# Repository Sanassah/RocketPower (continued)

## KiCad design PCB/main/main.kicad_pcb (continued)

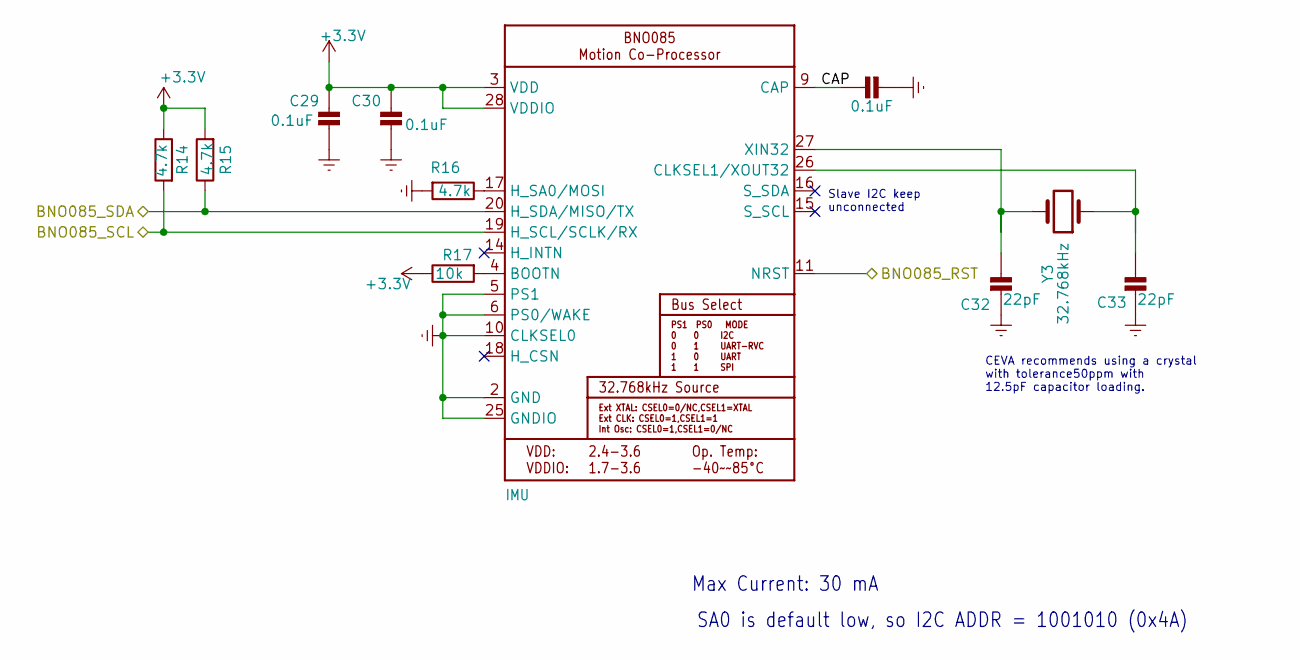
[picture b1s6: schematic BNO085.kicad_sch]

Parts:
BNO1: IMU; BNO085; Mouser Part Number 526-BNO085; LCSC C5189642
C29, C30, C31: 0.1uF; R_0603_1608Metric_Pad0.98x0.95mm_HandSolder; LCSC C1590
C32, C33: 22pF; R_0603_1608Metric_Pad0.98x0.95mm_HandSolder; LCSC C49326308
R14, R15, R16: 4.7k; R_0603_1608Metric_Pad0.98x0.95mm_HandSolder; LCSC C23162
R17: 10k; R_0603_1608Metric_Pad0.98x0.95mm_HandSolder; LCSC C25804
Y3: 32.768kHz; Crystal_SMD_2012-2Pin_2.0x1.2mm_HandSoldering; Mouser Part Number 815-ABS06-32.7K-1-T; LCSC C1985397

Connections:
+3.3V: BNO1.3 (VDD), BNO1.28 (VDDIO), C29.1, C30.1, R14.1, R15.2, R17.1; also elsewhere on the board
/BNO085_RST: BNO1.11 (NRST); also elsewhere on the board
/BNO085_SCL: BNO1.19 (H_SCL/SCLK/RX), R14.2; also elsewhere on the board
/BNO085_SDA: BNO1.20 (H_SDA/MISO/TX), R15.1; also elsewhere on the board
/IMU BNO085/CAP: BNO1.9 (CAP), C31.2
GNDREF: BNO1.2 (GND), BNO1.5 (PS1), BNO1.6 (PS0/WAKE), BNO1.10 (CLKSEL0), BNO1.25 (GNDIO), C29.2, C30.2, C31.1, C32.2, C33.2, R16.2; also elsewhere on the board
unnamed: BNO1.4 (BOOTN), R17.2
unnamed: BNO1.26 (CLKSEL1/XOUT32), C33.1, Y3.1
unnamed: BNO1.17 (H_SA0/MOSI), R16.1
unnamed: BNO1.27 (XIN32), C32.1, Y3.2

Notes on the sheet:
Max Current: 30 mA
SA0 is default low, so I2C ADDR = 1001010 (0x4A)
CEVA recommends using a crystal with tolerance50ppm with 12.5pF capacitor loading.
Slave I2C keep unconnected

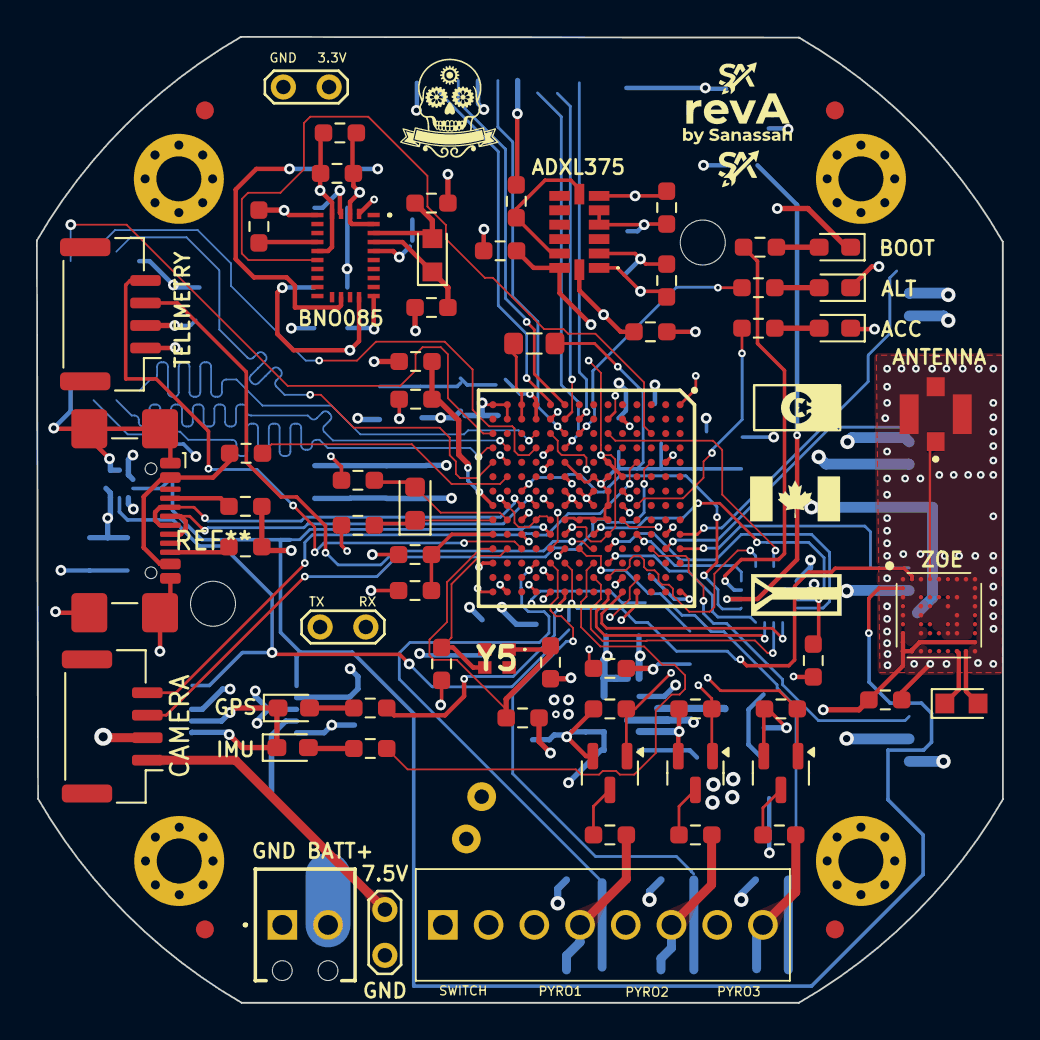
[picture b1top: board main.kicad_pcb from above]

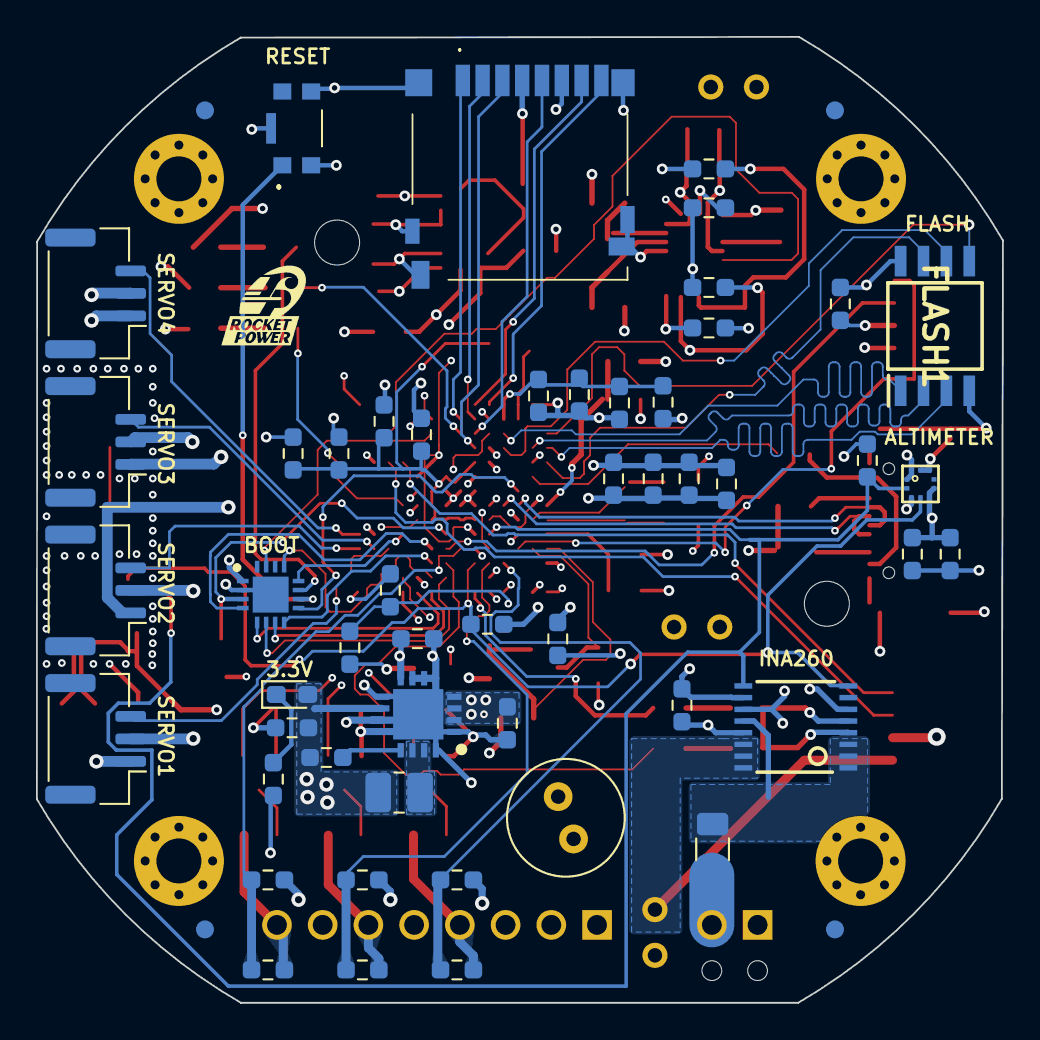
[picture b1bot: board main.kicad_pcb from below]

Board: 4 copper layers, 53.7 x 53.7 mm, 121 parts (55 on the bottom side), 97 nets.

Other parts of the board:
ADXL1: ACC; ADXL375BCCZRL
BMP1: ALTIMETER; BMP388
C34, C35, C37, C40: 0.1uF; R_0603_1608Metric_Pad0.98x0.95mm_HandSolder
C36: 1uF; R_0603_1608Metric_Pad0.98x0.95mm_HandSolder
INA1: INA260; TSSOP16
JST-GH-2: CAMERA; JST_GH_BM04B-GHS-TBT_1x04-1MP_P1.25mm_Vertical
R18, R32: 4.7k; R_0603_1608Metric_Pad0.98x0.95mm_HandSolder
R19: 10k; R_0603_1608Metric_Pad0.98x0.95mm_HandSolder
TP1, TP2, TP3: TestPoint_2Pole; TestPoint_2Pads_Pitch2.54mm_Drill0.8mm

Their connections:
+3.3V: ADXL1.1 (VDD(I/O)), ADXL1.6 (VIN), BMP1.1 (VDDIO), BMP1.5 (SDO), BMP1.6 (CSB), BMP1.10 (VDD), C34.1, C35.1, C36.1, C37.1, C40.1, INA1.10 (VS), R18.1, R19.1, R32.1, TP1.1; also elsewhere on the board
+7.5V: INA1.14 (IN-), INA1.15 (IN-), INA1.16 (IN-), JST-GH-2.1, TP3.1; also elsewhere on the board
+BATT: INA1.1 (IN+), INA1.2 (IN+), INA1.3 (IN+), INA1.12 (VBUS); also elsewhere on the board
/ADXL375_SCL2: ADXL1.14 (SCL), R32.2; also elsewhere on the board
/ADXL375_SDA2: ADXL1.13 (SDA), R18.2; also elsewhere on the board
/BMP390_SCL1: BMP1.2 (SCK), INA1.9 (SCL); also elsewhere on the board
/BMP390_SDA1: BMP1.4 (SDI), INA1.8 (SDA); also elsewhere on the board
/Cam_RX: JST-GH-2.3; also elsewhere on the board
/Cam_TX: JST-GH-2.4; also elsewhere on the board
/Reserve_RX: TP2.2; also elsewhere on the board
/Reserve_TX: TP2.1; also elsewhere on the board
GNDREF: ADXL1.2 (GND@1), ADXL1.4 (GND@2), ADXL1.5 (GND@3), BMP1.3 (GND), BMP1.8 (GND), BMP1.9 (GND), C34.2, C35.2, C36.2, C37.2, C40.2, INA1.4 (A1), INA1.5 (A0), INA1.6 (GND), INA1.11 (GND), INA1.13 (GND), JST-GH-2.2, TP1.2, TP3.2; also elsewhere on the board
unnamed: ADXL1.7 (CS), ADXL1.12 (ADDR/SDO), R19.2

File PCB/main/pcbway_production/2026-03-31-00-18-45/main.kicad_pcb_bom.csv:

Designator,Quantity,Value,Footprint,Package,MPN,DNP,Mount_Type,LCSC,Mouser Part Number,Rating,Description,Type,Height,Mouser Price/Stock,Manufacturer_Name,Arrow Part Number,Arrow Price/Stock,MANUFACTURER
ADXL1,1,ACC,ADXL375BCCZRL,,,,smt,C579466 ,584-ADXL375BCCZ,,,,,,,,,
BMP1,1,ALTIMETER,BMP388,,,,tht,C2684802 ,262-BMP390,,,,,,,,,
BNO1,1,IMU,BNO085,,,,smt,C5189642,526-BNO085,,,,,,,,,
"C1, C11, C28",3,10uF,R_0603_1608Metric_Pad0.98x0.95mm_HandSolder,,,,smt,C70225 ,,25V,,,,,,,,
"C10, C9",2,18pF,R_0603_1608Metric_Pad0.98x0.95mm_HandSolder,,,,smt,C1647 ,,,,,,,,,,
"C12, C13, C17, C18, C19, C20, C21, C22, C26, C5",10,0.22uF,R_0603_1608Metric_Pad0.98x0.95mm_HandSolder,,,,smt,C106216,,,,,,,,,,
"C14, C15, C16, C27, C38, C8",6,4.7uF,R_0603_1608Metric_Pad0.98x0.95mm_HandSolder,,,,smt,C19666 ,,,X5R 4U7 10% 6.3 V,,,,,,,
C2,1,22uF,R_0603_1608Metric_Pad0.98x0.95mm_HandSolder,,,,smt,C2762594,,6.3V,,,,,,,,
"C23, C24",2,10pF,R_0603_1608Metric_Pad0.98x0.95mm_HandSolder,,,,smt,C2168929,,,,,,,,,,
"C25, C7",2,10nF,R_0603_1608Metric_Pad0.98x0.95mm_HandSolder,,,,smt,C149619 ,,,,,,,,,,
"C29, C30, C31, C34, C35, C37, C39",7,0.1uF,R_0603_1608Metric_Pad0.98x0.95mm_HandSolder,,,,smt,C48579250,,,,Ceramic,,,,,,
"C3, C36, C40",3,1uF,R_0603_1608Metric_Pad0.98x0.95mm_HandSolder,,,,smt,C1592 ,,,,Tantalum,,,,,,
"C32, C33",2,22pF,R_0603_1608Metric_Pad0.98x0.95mm_HandSolder,,,,smt,C49326308 ,,,,,,,,,,
C41,1,470uf,C_Radial_D6.3mm_H11.0mm_P2.50mm,,,,tht,C1020067,,,"Polarized capacitor, 16v",,,,,,,
C6,1,2.2uF,R_0603_1608Metric_Pad0.98x0.95mm_HandSolder,,,,smt,C23630 ,,,,,,,,,,
CONMHF1-SMD-G-T1,1,ANTENNA,CONMHF1SMDGT,,CONMHF1-SMD-G-T,,smt,C22442695 ,712-CONMHF1-SMD-G-T,,CONMHF1-SMD-G-T,,1.31,https://www.mouser.co.uk/ProductDetail/TE-Connectivity-Linx-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,TE Connectivity,,,
D1,1,3.3V LED,LED_0603_1608Metric_Pad1.05x0.95mm_HandSolder,,,,smt,C20433785 ,78-TLMG1100-GS15,,,,,,,,,
D2,1,BOOT LED,LED_0603_1608Metric_Pad1.05x0.95mm_HandSolder,,,,smt,C20433785 ,78-TLMG1100-GS15,,,,,,,,,
D3,1,GPS LED,LED_0603_1608Metric_Pad1.05x0.95mm_HandSolder,,,,smt,C20433785 ,78-TLMG1100-GS15,,,,,,,,,
D4,1,Altimeter LED,LED_0603_1608Metric_Pad1.05x0.95mm_HandSolder,,,,smt,C20433785 ,78-TLMG1100-GS15,,,,,,,,,
D5,1,200G ACC LED,LED_0603_1608Metric_Pad1.05x0.95mm_HandSolder,,,,smt,C20433785 ,78-TLMG1100-GS15,,,,,,,,,
D6,1,IMU LED,LED_0603_1608Metric_Pad1.05x0.95mm_HandSolder,,,,smt,C20433785 ,78-TLMG1100-GS15,,,,,,,,,
D7,1,ESD9R3.3ST5G,ESD9R3_3ST5G,,ESD9R3.3ST5G,,smt,C233388 ,863-ESD9R3.3ST5G,,Low Body Height: 0.016 (0.4 mm); Small Body Outline Dimensions: 0.039 x 0.024 (1.00 mm x 0.60 mm); UltraLow Leakage < 1 nA; UltraLow Capacitance 0.5 pF; Low Clamping Voltage; Standoff Voltage: 3.3 V; Response Time < 1.0 ns; IEC6100042 Level 4 ESD Protection; This is a PbFree and HalogenFree Device,,0.4,https://www.mouser.co.uk/ProductDetail/onsemi/ESD9R3.3ST5G?q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,onsemi,,,
DM3D-SF1,1,MicroSD,DM3DSF,,DM3D-SF,,smt,C719027 ,798-DM3D-SF,,Micro SD card push pull manual,,1.55,https://www.mouser.co.uk/ProductDetail/Hirose-Connector/DM3D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,Hirose,,,
F1,1,6A,Fuse_1206_3216Metric,,,,smt,C183157 ,530-C1F6,,,PPTC,,,,,,
"FB1, FB2",2,120,R_0603_1608Metric_Pad0.98x0.95mm_HandSolder,,,,smt,C14709,81-BLM18PG121SN1D,,Ferrite bead,,,,,,,
INA1,1,INA260,TSSOP16,,,,tht,C2155885 ,595-INA260AIPWR,,,,,,,,,
KMR241GLFS1,1,RESET,KMR421GULCLFS,,KMR241GLFS,,smt,C221682 ,611-KMR241GLFS,,KMR241GLFS,,2.5,https://www.mouser.co.uk/ProductDetail/CK/KMR241GLFS?qs=sb%2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,C & K COMPONENTS,,,
L1,1,6.8uH,L_1008_2520Metric_Pad1.43x2.20mm_HandSolder,,,,smt,C307868 ,810-VLS25212HBX6R8M1,,,,,,,,,
L2,1,4.7uH,L_0805_2012Metric_Pad1.05x1.20mm_HandSolder,,,,smt,C397305 ,81-LQM21PN4R7NGRDRD,,,,,,,,,
L3,1,2.2μH,L_0805_2012Metric_Pad1.05x1.20mm_HandSolder,,,,smt,C83998,81-LQM2MPN2R2NG0L,,LQM2MPN2R2NG0L,,,,,,,
MIMXRT1062DVL6B1,1,MCU,BGA196C80P14X14_1200X1200X152,,MIMXRT1062DVL6B,,smt,C2847497,771-MIMXRT1062DVL6B,,MIMXRT1062DVL6B,,1.52,https://www.mouser.co.uk/ProductDetail/NXP-Semiconductors/MI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,NXP,MIMXRT1062DVL6B,https://www.arrow.com/en/products/mimxrt1062dvl6b/nxp-semico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,
MKL02Z32VFG1,1,BOOT,QFN50P300X300X65-17N-D,,MKL02Z32VFG4,Yes,smt,,,,MKL02Z32VFG4,,0.65,https://www.mouser.co.uk/ProductDetail/NXP-Semiconductors/MK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,NXP,MKL02Z32VFG4,https://www.arrow.com/en/products/mkl02z32vfg4/nxp-semicondu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,
"Q1, Q2, Q3",3,SI2302,SOT-23,,,,smt,C460978,621-DMG3406L-7,,,,,,,,,
"R1, R2",2,5.1k,R_0603_1608Metric_Pad0.98x0.95mm_HandSolder,,,,smt,C1647,,,,,,,,,,
R10,1,2.2M,R_0603_1608Metric_Pad0.98x0.95mm_HandSolder,,,,smt,C18679 ,,,,,,,,,,
"R11, R12, R5, R7, R9",5,470,R_0603_1608Metric_Pad0.98x0.95mm_HandSolder,,,,smt,C23179,,,,,,,,,,
R13,1,100k,R_0603_1608Metric_Pad0.98x0.95mm_HandSolder,,,,smt,C14675,,,,,,,,,,
"R14, R15, R16, R6, R8",5,4.7k,R_0603_1608Metric_Pad0.98x0.95mm_HandSolder,,,,smt,C23162 ,,,,,,,,,,
"R17, R18, R19, R20, R23, R24, R27, R28, R31",9,10k,R_0603_1608Metric_Pad0.98x0.95mm_HandSolder,,,,smt,C25804 ,,,,,,,,,,
"R21, R25, R29",3,7,R_0603_1608Metric_Pad0.98x0.95mm_HandSolder,,,,smt,C228062 ,,,,,,,,,,
"R22, R26, R30",3,7k,R_0603_1608Metric_Pad0.98x0.95mm_HandSolder,,,,smt,C23101 ,,,,,,,,,,
R3,1,1M,R_0603_1608Metric_Pad0.98x0.95mm_HandSolder,,,,smt,C22935,,,,,,,,,,
R4,1,1k,R_0603_1608Metric_Pad0.98x0.95mm_HandSolder,,,,smt,C21190 ,,,,,,,,,,
S4B-PH-K-S_LF__SN_1,1,TELEMETRY,JST_GH_BM04B-GHS-TBT_1x04-1MP_P1.25mm_Vertical,,S4B-PH-K-S(LF)(SN),,smt,C161692,306-BM04BGHSTBTLFSNN,,CONN HEADER R/A 4POS 2MM,,4.8,https://www.mouser.co.uk/ProductDetail/JST-Commercial/S4B-PH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,JST (JAPAN SOLDERLESS TERMINALS),,,
S4B-PH-K-S_LF__SN_2,1,CAMERA,JST_GH_BM04B-GHS-TBT_1x04-1MP_P1.25mm_Vertical,,S4B-PH-K-S(LF)(SN),,smt,C161692,306-BM04BGHSTBTLFSNN,,CONN HEADER R/A 4POS 2MM,,4.8,https://www.mouser.co.uk/ProductDetail/JST-Commercial/S4B-PH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,JST (JAPAN SOLDERLESS TERMINALS),,,
SERVO1,1,SERVO1,JST_GH_BM03B-GHS-TBT_1x03-1MP_P1.25mm_Vertical,,,,smt,C161691,306-BM03BGHSTBTLFSNN,,,,,,,,,
SERVO2,1,SERVO2,JST_GH_BM03B-GHS-TBT_1x03-1MP_P1.25mm_Vertical,,,,smt,C161691,306-BM03BGHSTBTLFSNN,,,,,,,,,
SERVO3,1,SERVO3,JST_GH_BM03B-GHS-TBT_1x03-1MP_P1.25mm_Vertical,,,,smt,C161691,306-BM03BGHSTBTLFSNN,,,,,,,,,JST
SERVO4,1,SERVO4,JST_GH_BM03B-GHS-TBT_1x03-1MP_P1.25mm_Vertical,,,,smt,C161691,306-BM03BGHSTBTLFSNN,,,,,,,,,
ScrewTerminal1,1,1725711,1725711,,1725711,,tht,C5476987,651-1725711,,"PCB terminal block - MPT 0,5/ 8-2,54 - 1725711",,8.65,https://www.mouser.co.uk/ProductDetail/Phoenix-Contact/17257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,Phoenix Contact,,,
ScrewTerminal2,1,BATT,1725656,,,,tht,C3029316 ,651-1725656,,"Generic screw terminal, single row, 01x02, script generated (kicad-library-utils/schlib/autogen/connector/)",,,,,,,
TP1,1,TestPoint_2Pole,TestPoint_2Pads_Pitch2.54mm_Drill0.8mm,,,Yes,tht,,,,2-polar test point,,,,,,,
TP2,1,TestPoint_2Pole,TestPoint_2Pads_Pitch2.54mm_Drill0.8mm,,,Yes,tht,,,,2-polar test point,,,,,,,
TP3,1,TestPoint_2Pole,TestPoint_2Pads_Pitch2.54mm_Drill0.8mm,,,Yes,tht,,,,2-polar test point,,,,,,,
TPS62111RSAR1,1,3.3Vreg,TPS62111RSAR,,TPS62111RSAR,,smt,C133558 ,595-TPS62111RSAR,,,,1,https://www.mouser.co.uk/ProductDetail/Texas-Instruments/TPS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,Texas Instruments,,,
U-BLOX_ZOE_M8Q-0-1,1,GPS,UBLOX_ZOE_M8-0-10,,,,tht,C7398634,377-ZOE-M8Q-0,,U-BLOX_ZOE_M8Q-0-10,,,,,,,
USB_C_Receptacle_USB2.0_14P1,1,USBc,USB_C_Receptacle_GCT_USB4110,,,,smt,C5143397,640-USB4110-GF-A,,USB_C_Receptacle_USB2.0_14P,,,,,,,
W25Q64JVXGIM_TR1,1,FLASH,SON80P400X400X50-9N,,W25Q64JVXGIM TR,,smt,C7398634 ,454-W25Q64JVXGIMTR,,W25Q64JVXGIM_TR,,0.5,https://www.mouser.co.uk/ProductDetail/Winbond/W25Q64JVXGIM-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,Winbond,,,
"Y1, Y3",2,32.768kHz,Crystal_SMD_2012-2Pin_2.0x1.2mm_HandSoldering,,,,smt,[Y1]C510776; [Y3]C1985397,[Y1]815-ABS06-32.7K-9-T; [Y3]815-ABS06-32.7K-1-T,,50ppm  -  12.5pF capacitor loading,,,,,,,
Y4,1,32.768kHz,830050789,,,,smt,C7462219,428-202816-MC01,,7 pF  +/- 100 ppm   70 kOhms,,,,,,,
Y5,1,XRCGB24M000F2P29R0,XRCGB,,XRCGB24M000F2P29R0,,smt, C7397287 ,81-XRCGB24M000F2P29R,,"24 MHz +/-20ppm Crystal 8pF 80 Ohms 4-SMD, No Lead",,0.7,https://www.mouser.co.uk/ProductDetail/Murata-Electronics/XR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,Murata Electronics,,,

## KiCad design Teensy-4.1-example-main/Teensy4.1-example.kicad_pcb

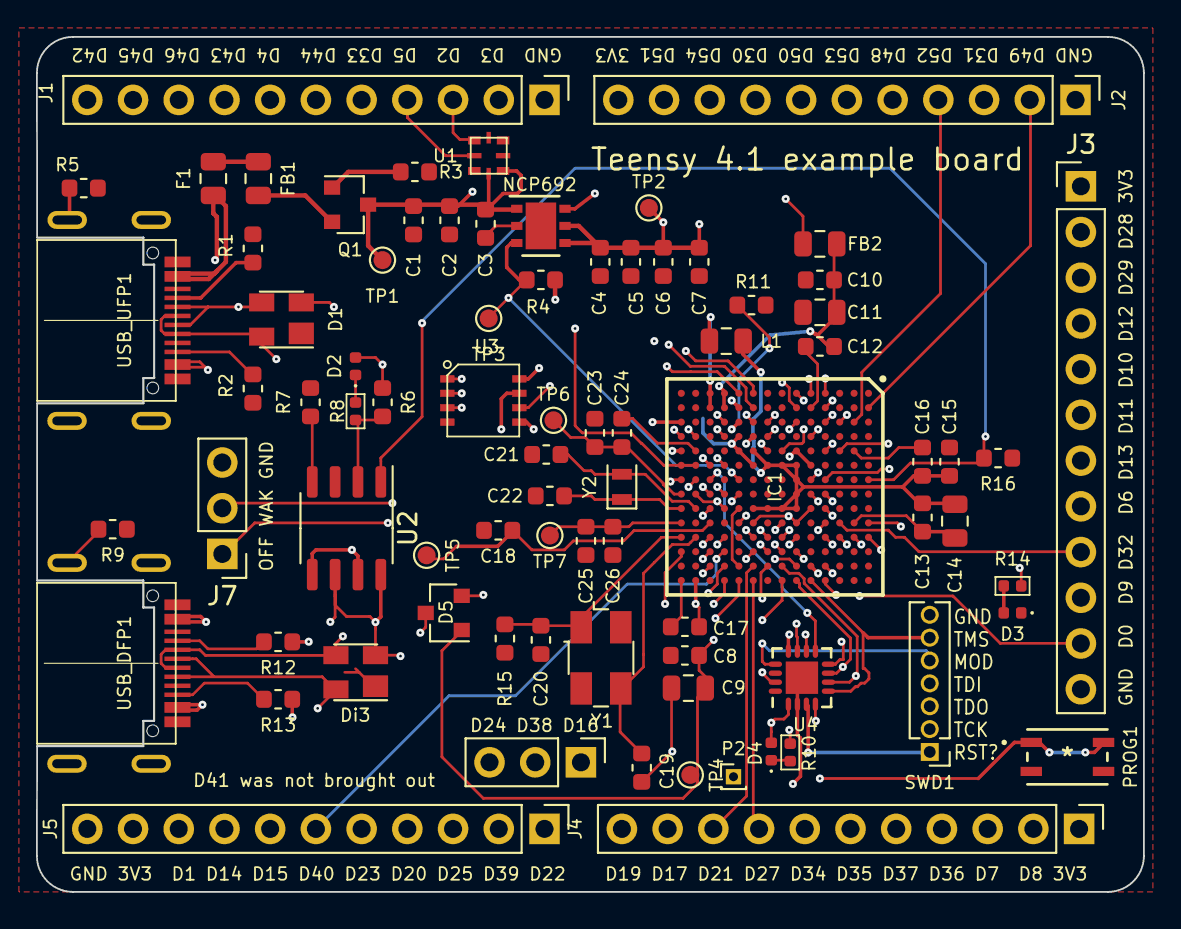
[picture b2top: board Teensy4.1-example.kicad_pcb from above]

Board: 4 copper layers, 61.5 x 47.5 mm, 80 parts (0 on the bottom side), 109 nets.

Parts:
C1, C2, C4, C8, C10, C13, C17, C18, C23, C25: 0.22uf; C_0603_1608Metric
C3, C7: 2.2uf; C_0603_1608Metric
C5, C16: 10nf; C_0603_1608Metric
C6, C12, C15, C24, C26: 4.7uf; C_0603_1608Metric
C9, C11, C14: 10uf; C_0805_2012Metric
C19, C20: 10pf; C_0603_1608Metric
C21, C22: 9pf; C_0603_1608Metric
D1: SP0503BAHT; SOT-143
D2, D3, D4: LED; LED_0402_1005Metric
D5: BAT54C; SOT-23
Di3: SP0503BAHT; SOT-143
F1: Fuse; R_0805_2012Metric
FB1, FB2: Ferrite_Bead; R_0805_2012Metric
IC1: MIMXRT1062DVJ6B; BGA196C80P14X14_1200X1200X152
J1, J2, J4, J5: Conn_01x11_Male; PinHeader_1x11_P2.54mm_Vertical
J3: Conn_01x12_Male; PinHeader_1x12_P2.54mm_Vertical
J6, J7: Conn_01x03_Male; PinHeader_1x03_P2.54mm_Vertical
L1: 4.7uH; C_0805_2012Metric
NCP692: OnSemi NCP692, fixed version; DFN-6-1EP_3x3mm_P0.95mm_EP1.7x2.6mm
P2: D26; PinHeader_1x01_P1.00mm_Vertical
PROG1: SW_Push; KMR241GLFS
Q1: Q_PMOS_GDS; SOT-23
R1, R2: 5.1k; R_0603_1608Metric
R3, R4, R11, R16: 100k; R_0603_1608Metric
R5, R9: 1M; R_0603_1608Metric
R6, R7: 16k; R_0603_1608Metric
R8, R10, R14: 1k; R_0402_1005Metric
R12, R13: 56k; R_0603_1608Metric
R15: 2.2M; R_0603_1608Metric
SWD1: SWD; PinHeader_1x07_P1.27mm_Vertical
TP1, TP2, TP3, TP4, TP5, TP6, TP7: TestPoint; TestPoint_Pad_D1.0mm
U1: opto_APA102-2020; APA102-2020
U2: MAX1562; SO-8_3.9x4.9mm_P1.27mm
U3: W25Q64JVXGIM; XSON8_4x4mm
U4: MKL02Z32VFG4; QFN-16-1EP_3x3mm_P0.5mm_EP1.8x1.8mm
USB_DFP1: USB_C_Receptacle_USB2.0; TYPE-C-31-M-14
USB_UFP1: USB_C_Receptacle_USB2.0; TYPE-C-31-M-14
Y1: Crystal_GND23; Crystal_SMD_Abracon_ABM3B-4Pin_5.0x3.2mm
Y2: Crystal; Crystal_SMD_2012-2Pin_2.0x1.2mm

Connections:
+3V3: C4.1, C5.1, C6.1, C7.1, C17.1, D4.2 (A), D5.2, FB2.2, IC1.E6 (NVCC_EMC_1), IC1.E9 (NVCC_GPIO_1), IC1.F5 (NVCC_EMC_2), IC1.F10 (NVCC_GPIO_2), IC1.J6 (NVCC_SD0), IC1.J10 (NVCC_GPIO_3), IC1.K4 (DCDC__IN_Q), IC1.K5 (NVCC_SD1), IC1.N14 (VDDA_ADC_3P3), IC1.P12 (VDD_HIGH_IN), J2.11, J3.1, J4.1, J5.10, NCP692.4 (OUT), NCP692.5 (SNS), R4.2, TP2.1, U3.8 (VDD), U4.1 (VDD/VREFH)
+5V: C1.1, C2.1, C3.1, IC1.N6 (USB_OTG1_VBUS), IC1.P6 (USB_OTG2_VBUS), NCP692.1 (IN), NCP692.6 (IN), Q1.3 (S), TP1.1, U1.1 (VDD)
+5VD: D1.2 (K), D2.2 (A), F1.1, R6.1, U2.5 (IN), U2.7 (IN), USB_UFP1.A4 (VBUS), USB_UFP1.A9 (VBUS), USB_UFP1.B4 (VBUS), USB_UFP1.B9 (VBUS)
+5VL: Di3.2 (K), R12.1, R13.1, U2.6 (OUT), U2.8 (OUT), USB_DFP1.A4 (POW), USB_DFP1.A9 (POW), USB_DFP1.B4 (POW), USB_DFP1.B9 (POW)
/D0: IC1.G11 (GPIO_AD_B0_03), J3.11
/D1: IC1.M11 (GPIO_AD_B0_02), J5.9
/D2: IC1.F2 (GPIO_EMC_04), J1.3, U1.4 (SDI)
/D3: IC1.G5 (GPIO_EMC_05), J1.2
/D4: IC1.H5 (GPIO_EMC_06), J1.7
/D5: IC1.H3 (GPIO_EMC_08), J1.4, U1.5 (CKI)
/D6: IC1.D9 (GPIO_B0_10), J3.8
/D7: IC1.B11 (GPIO_B1_01), J4.3
/D8: IC1.A11 (GPIO_B1_00), J4.2
/D9: IC1.A10 (GPIO_B0_11), J3.10
/D10: IC1.D7 (GPIO_B0_00), J3.5
/D11: IC1.E8 (GPIO_B0_02), J3.6
/D12: IC1.E7 (GPIO_B0_01), J3.4
/D13: IC1.D8 (GPIO_B0_03), J3.7, R14.1
/D14_A0: IC1.L11 (GPIO_AD_B1_02), J5.8
/D15_A1: IC1.M12 (GPIO_AD_B1_03), J5.7
/D16_A2: IC1.K10 (GPIO_AD_B1_07), J6.1
/D17_A3: IC1.J12 (GPIO_AD_B1_06), J4.10
/D19_A5: IC1.J11 (GPIO_AD_B1_00), J4.11
/D20_A6: IC1.L13 (GPIO_AD_B1_10), J5.4
/D21_A7: IC1.J13 (GPIO_AD_B1_11), J4.9
/D22_A8: IC1.H13 (GPIO_AD_B1_08), J5.1
/D23_A9: IC1.M13 (GPIO_AD_B1_09), J5.5
/D24_A10: IC1.K14 (GPIO_AD_B0_12), J6.3
/D25_A11: IC1.L14 (GPIO_AD_B0_13), J5.3
/D26_A12: IC1.G12 (GPIO_AD_B1_14), P2.1
/D27_A13: IC1.J14 (GPIO_AD_B1_15), J4.8
/D28: IC1.D5 (GPIO_EMC_32), J3.2
/D29: IC1.C5 (GPIO_EMC_31), J3.3
/D30: IC1.E4 (GPIO_EMC_37), J2.8
/D31: IC1.C3 (GPIO_EMC_36), J2.3
/D32: IC1.C10 (GPIO_B0_12), J3.9
/D33: IC1.H4 (GPIO_EMC_07), J1.5
/D34: IC1.D14 (GPIO_B1_13), J4.7
/D35: IC1.D13 (GPIO_B1_12), J4.6
/D36: IC1.C11 (GPIO_B1_02), J4.4
/D37: IC1.D11 (GPIO_B1_03), J4.5
/D38_A14: IC1.H12 (GPIO_AD_B1_12), J6.2
/D39_A15: IC1.H11 (GPIO_AD_B1_13), J5.2
/D40_A16: IC1.L12 (GPIO_AD_B1_04), J5.6
/D42: IC1.K1 (GPIO_SD_B0_03), J1.11
/D43: IC1.J1 (GPIO_SD_B0_02), J1.8
/D44: IC1.J3 (GPIO_SD_B0_01), J1.6
/D45: IC1.J4 (GPIO_SD_B0_00), J1.10
/D46: IC1.J2 (GPIO_SD_B0_05), J1.9
/D48: IC1.D3 (GPIO_EMC_24), J2.5
/D49: IC1.A2 (GPIO_EMC_27), J2.2
/D50: IC1.D1 (GPIO_EMC_28), J2.7
/D51: IC1.F1 (GPIO_EMC_22), J2.10
/D52: IC1.B3 (GPIO_EMC_26), J2.4
/D53: IC1.D2 (GPIO_EMC_25), J2.6
/D54: IC1.E1 (GPIO_EMC_29), J2.9
/DCDC_PSWITCH: IC1.G10 (GPIO_AD_B0_11), IC1.K3 (DCDC_PSWITCH), R11.2, SWD1.1, U4.3 (PTA3)
/JTAG_MOD: IC1.F13 (GPIO_AD_B0_08), SWD1.5, U4.13 (PTB5/IRQ_12)
/JTAG_TCK: IC1.F12 (GPIO_AD_B0_07), SWD1.2, U4.8 (PTB0/IRQ_5)
/JTAG_TDI: IC1.F14 (GPIO_AD_B0_09), SWD1.4, U4.7 (PTA7/IRQ_4)
/JTAG_TDO: IC1.G13 (GPIO_AD_B0_10), SWD1.3, U4.6 (PTA6)
/JTAG_TMS: IC1.E14 (GPIO_AD_B0_06), SWD1.6, U4.5 (PTA5)
/ONOFF: IC1.M6 (ONOFF), J7.1
/PMIC_ON_REQ_PWR_SEQ: IC1.K7 (PMIC_ON_REQ), NCP692.3 (EN), R4.1, TP3.1
/POR_B: IC1.M7 (POR_B), U4.9 (PTB1/IRQ_6)
/SOC_CAP_NET: C13.1, C14.1, C15.1, C16.1, IC1.F6 (VDD_SOC_IN_1), IC1.F7 (VDD_SOC_IN_2), IC1.F8 (VDD_SOC_IN_3), IC1.F9 (VDD_SOC_IN_4), IC1.G6 (VDD_SOC_IN_5), IC1.G9 (VDD_SOC_IN_6), IC1.H6 (VDD_SOC_IN_7), IC1.H9 (VDD_SOC_IN_8), IC1.J5 (DCDC_SENSE), IC1.J9 (VDD_SOC_IN_9), L1.2
/USB1_DN: D1.3 (K), IC1.M8 (USB_OTG1_DN), USB_UFP1.A7 (D-), USB_UFP1.B7 (D-)
/USB1_DP: D1.4 (K), IC1.L8 (USB_OTG1_DP), USB_UFP1.A6 (D+), USB_UFP1.B6 (D+)
/USB2_DN: Di3.3 (K), IC1.N7 (USB_OTG2_DN), USB_DFP1.A7 (D-), USB_DFP1.B7 (D-)
/USB2_DP: Di3.4 (K), IC1.P7 (USB_OTG2_DP), USB_DFP1.A6 (D+), USB_DFP1.B6 (D+)
/WAKEUP: IC1.L6 (WAKEUP), J7.2
GND: C1.2, C2.2, C3.2, C4.2, C5.2, C6.2, C7.2, C8.2, C9.2, C10.2, C11.2, C12.2, C13.2, C14.2, C15.2, C16.2, C17.2, C18.2, C19.2, C20.2, C21.2, C22.2, C23.2, C24.2, C25.2, C26.2, D1.1 (A), D3.1 (K), Di3.1 (A), IC1.A1 (VSS_1), IC1.A14 (VSS_2), IC1.B5 (VSS_3), IC1.B10 (VSS_4), IC1.E2 (VSS_5), IC1.E13 (VSS_6), IC1.G7 (VSS_7), IC1.G8 (VSS_8), IC1.G14 (GPIO_AD_B0_05), IC1.H7 (VSS_9), IC1.H8 (VSS_10), IC1.J7 (VSS_11), IC1.J8 (VSS_12), IC1.K2 (VSS_13), IC1.K9 (NGND_KEL0), IC1.K13 (VSS_14), IC1.L9 (VSS_15), IC1.N1 (DCDC_GND_1), IC1.N2 (DCDC_GND_2), IC1.N5 (VSS_16), IC1.N8 (VSS_17), IC1.P1 (VSS_18), IC1.P14 (VSS_19), J1.1, J2.1, J3.12, J5.11, J7.3, NCP692.2 (GND), NCP692.7 (GND), PROG1.2, R1.1, R2.1, R3.1, R5.1, R7.1, R9.1, R11.1, R15.1, R16.1, SWD1.7, U1.6 (GND), U2.3 (GND), U3.4 (GND), U4.2 (VSS/VREFL), U4.17 (EPAD), USB_DFP1.A1 (GND), USB_DFP1.A12 (GND), USB_DFP1.B1 (GND), USB_DFP1.B12 (GND), USB_UFP1.A1 (GND), USB_UFP1.A12 (GND), USB_UFP1.B1 (GND), USB_UFP1.B12 (GND), Y1.2, Y1.4
unnamed: C8.1, C9.1, D5.1, IC1.K8 (VDD_USB_CAP), TP4.1
unnamed: C10.1, C11.1, C12.1, FB2.1, IC1.L1 (DCDC_IN_1), IC1.L2 (DCDC_IN_2)
unnamed: C18.1, IC1.M10 (VDD_SNVS_CAP), TP5.1
unnamed: C19.1, IC1.N11 (XTALO), Y1.3
unnamed: C20.1, IC1.P11 (XTALI), R15.2, Y1.1
unnamed: C21.1, IC1.N9 (RTC_XTALI), Y2.2
unnamed: C22.1, IC1.P9 (RTC_XTALO), Y2.1
unnamed: C23.1, C24.1, IC1.P8 (VDD_HIGH_CAP), TP6.1
unnamed: C25.1, C26.1, IC1.P10 (NVCC_PLL), TP7.1
unnamed: D2.1 (K), R8.1
unnamed: D3.2 (A), R14.2
unnamed: D4.1 (K), R10.2
unnamed: D5.3, IC1.M9 (VDD_SNVS_IN)
unnamed: F1.2, FB1.1
unnamed: FB1.2, Q1.2 (D)
unnamed: IC1.A7 (GPIO_EMC_40), R16.2, U2.1 (ON)
unnamed: IC1.D10 (GPIO_B0_13), U4.12 (PTB4/IRQ_11)
unnamed: IC1.F3 (GPIO_EMC_01), U4.15 (PTA1/IRQ_1/LPTMR0_ALT1)
unnamed: IC1.F11 (GPIO_AD_B0_04), U4.4 (PTA4)
unnamed: IC1.L3 (GPIO_SD_B1_06), U3.1 (CS)
unnamed: IC1.L4 (GPIO_SD_B1_07), U3.6 (CLK)
unnamed: IC1.M1 (DCDC_LP_1), IC1.M2 (DCDC_LP_2), L1.1
unnamed: IC1.N4 (GPIO_SD_B1_09), U3.2 (D1)
unnamed: IC1.P3 (GPIO_SD_B1_08), U3.5 (D0)
unnamed: IC1.P4 (GPIO_SD_B1_10), U3.3 (D2)
unnamed: IC1.P5 (GPIO_SD_B1_11), U3.7 (D3)
unnamed: PROG1.1, U4.10 (PTB2/IRQ_7)
unnamed: Q1.1 (G), R3.2
unnamed: R1.2, USB_UFP1.A5 (CC1)
unnamed: R2.2, USB_UFP1.B5 (CC2)
unnamed: R5.2, USB_UFP1.S1 (SHIELD)
unnamed: R6.2, R8.2, U2.2 (Fault)
unnamed: R7.2, U2.4 (ISET)
unnamed: R9.2, USB_DFP1.S1 (SHIELD)
unnamed: R10.1, U4.11 (PTB3/IRQ_10)
unnamed: R12.2, USB_DFP1.A5 (CC1)
unnamed: R13.2, USB_DFP1.B5 (CC2)

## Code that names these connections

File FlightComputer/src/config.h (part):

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// Wire2 (LPI2C4, pins 25 SDA / 24 SCL): sensors labelled _SDA2 / _SCL2

#define BNO085_I2C_BUS   Wire
#define BNO085_I2C_ADDR  0x4A   // SA0 pulled LOW (BNO085_SCL/SDA, no suffix)
#define BNO085_RESET_PIN 31    // BNO085_RST: MCU GPIO_EMC_36/C3 -> BNO NRST; active LOW

#define BMP390_I2C_BUS   Wire1
#define BMP390_I2C_ADDR  0x77   // SDO pulled HIGH (BMP390_SCL1/SDA1)

#define ZOEM8_I2C_BUS    Wire1
#define ZOEM8_I2C_ADDR   0x42   // fixed u-blox DDC address (ZOEM8_SCL1/SDA1)
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#define INA260_I2C_ADDR  0x40   // A0=A1=GND (INA260_SCL1/SDA1)

#define ADXL375_I2C_BUS  Wire2
#define ADXL375_I2C_ADDR 0x1D   // CS tied HIGH, ADDR tied HIGH (ADXL375_SCL2/SDA2)

// ===== IMU mounting-offset calibration =====
// BENCH-CONFIRMED (2026-09): the BNO085's rotation vector reports a fixed
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
// ===== UART Assignments =====
// From schematic text annotations: "0 (RX1)", "1 (TX1)", "RX 28", "TX 29"
#define LORA_SERIAL      Serial1   // Lora_TX→pin0 (RX1), Lora_RX→pin1 (TX1)
#define LORA_BAUD        9600

#define CAM_SERIAL       Serial7   // Cam_TX→pin28 (RX7), Cam_RX→pin29 (TX7)
#define CAM_BAUD         115200

// ===== LoRa E22-900T22D Control =====
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// ===== Pyro Channels =====
// Active-HIGH low-side MOSFET gates. Pin numbers follow the PCB's actual
// MCU pads and Teensy core mapping, NOT the legacy net-name suffixes.
// PyroCH2_3 and PyroCH3_4 are wired to Teensy pins 11 and 12, not 3 and 4.
// Pyrox_Test_N → continuity sense (analog input), MCU pin N
#define PYRO_CH1_FIRE_PIN   2     // PyroCH1_2: GPIO_EMC_04, F2 — parachute
#define PYRO_CH2_FIRE_PIN   11    // PyroCH2_3: GPIO_B0_02, E8 — reserved/manual
#define PYRO_CH3_FIRE_PIN   12    // PyroCH3_4: GPIO_B0_01, E7 — backup

#define PYRO_CH1_CONT_PIN   40    // Pyro1_Test_40
#define PYRO_CH2_CONT_PIN   41    // Pyro2_Test_41
#define PYRO_CH3_CONT_PIN   39    // Pyro3_Test_39

#define PYRO_NUM_CHANNELS   3
#define PYRO_FIRE_DURATION_MS  500     // pulse width when firing
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// JST-GH 4-pin, Serial7 at 115200 baud (RunCam Split 4-25 compatible)

// ===== Fin actuation servos =====
// From HighCurrentComponents.kicad_sch hierarchical labels Servo1_PWM..Servo4_PWM.
// Closed-loop attitude control exists (see AttitudeController) but is OFF by
// default -- see ATTITUDE_CONTROL_ENABLED below. Bench-test-only functions
// (testSweep, preflightSequence, trim nudge/save) are unaffected either way.
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
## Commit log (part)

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2024-10-04 First commit, this is my first version of the flight computer pcb design only with what is nesseray to make the MIMXRT106DVL6B MCU work
2024-10-12 Added the ADXL375 AND BMP390 to the schematic, next step is gps and sdcard holder
2024-10-15 Added a few sensors schematics like multiplex for i2c comms, current/voltage sensor, micro sd slot, more to go!
2024-10-24 Well I added a bunch of sensors, some connectors for battery, pyro channels mosfets, etc
2025-09-14 Addition of telemetry is pcb schematic
2025-12-22 The design is getting more mature, still did not choose if doing 4 layers or 2 layers pcb, will try to add 5v for a on board camera and trace routes for reserved pins in case of usage on another vehi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
2025-12-26 Reserved and camera sheets
2025-12-28 Camera and reserve
2025-12-29 CID documentation and started the PCB editor process
2026-02-02 Layout of PCB mostly done
2026-02-03 Preliminary layout done but need to rearrange sd card and such to have the best routing
2026-02-04 Routing pcb
2026-03-11 Addition of teensy example and milestone on routing completed, missing a few components to connect
2026-03-12 First iteration of layout finished, we could call this v0, congratulations! Need an expert to state if layer 4 and layer 3 interations are ok (pwm/ psram/i2c/uart vs power plane 7.5v and 3.3v )
2026-03-12 PR1; Fix PSRAM length of data, clock and cs pins to match since high speed data transmission, needs to be within 0.5mm trace length delta
2026-03-15 First pass of verification and validation of pcb design
2026-03-25 Layout changes to incorporate power capacitors for the servos
2026-03-28 Addition of all components in BOM, metal mounting plates, need to check psram if its ok for signals to pass under, all components need a double check
2026-03-31 Last commit before changing bga to trace clearance of 6mils
2026-04-01 First commit with 0.1mm traces and 02mm by 0.43mm vias to fit pcbway standard manufacturing + corrections of PR'S like uart RX of component to TX of mcu
2026-04-13 Switch to KICAD10 and correction of TX RX
2026-04-22 Change of winbond flash to other one supported by teensy bootloader since winbond is out of stock
2026-05-07 Final verification started, schematic verification of USBC and High current components
2026-05-17 Corrected a few subsystems
2026-05-17 Corrections of mistake, revision of schematic is done and BOM revised, revision of pcb layout to do
2026-05-17 Because i am lazy i would call this the V1 of the avionics
2026-05-18 Was missing pull ups on adxl375
2026-05-19 REVA board?
2026-05-22 Addition of logos silkscreen
2026-05-22 Logo update
2026-06-29 First Attempt to ground station code, flight computer code and correction for revB PCB (reset button)
